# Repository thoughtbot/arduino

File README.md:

arduino
=======

Public repo for thoughtbot custom Arduino board

Refer to these blog posts for instructions:

[Low Power Custom Arduino Sensor Board](http://robots.thoughtbot.com/low-power-custom-arduino-sensor-board)

[Arduino Sensor Network](http://robots.thoughtbot.com/arduino-sensor-network)

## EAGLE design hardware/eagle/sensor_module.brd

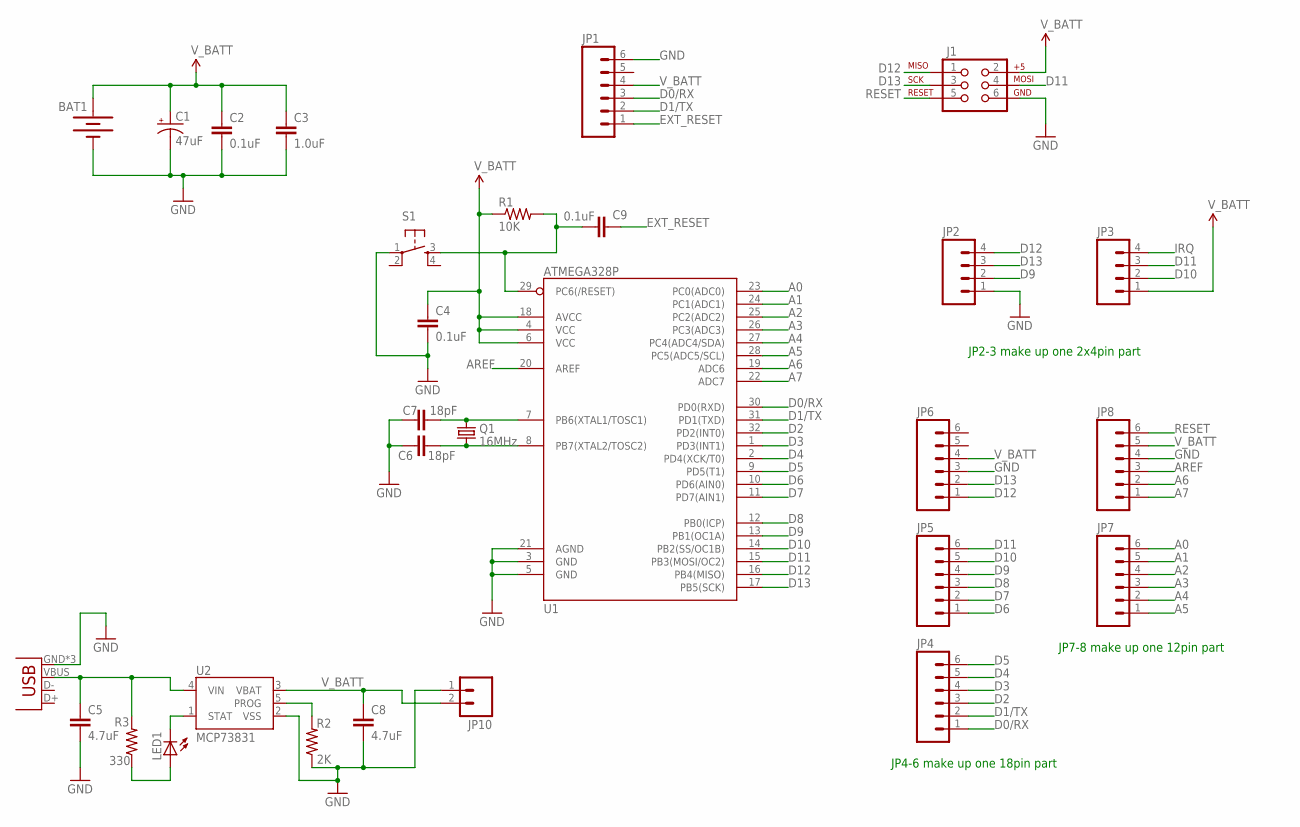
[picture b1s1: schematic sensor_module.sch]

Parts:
BAT1: 20mm coincell; BATTCON_20MM_4LEGS
C1: 47uF; EIA3216
C2, C4, C9: 0.1uF; 0603-CAP
C3: 1.0uF; 0603-CAP
C5, C8: 4.7uF; 0603-CAP
C6, C7: 18pF; 0603-CAP
J1: AVR_SPI_PRG_6PTH; 2X3
JP1, JP4, JP5, JP6, JP7, JP8: M06SIP; 1X06
JP2, JP3: M04PTH; 1X04
JP9: USB-MICROB
JP10: M02JST-PTH-2; JST-2-PTH
LED1: LED_ESML0603; LED_SML0603
Q1: 16MHz; HC49UP
R1: 10K; 0603-RES
R2: 2K; 0603-RES
R3: 330; 0603-RES
S1: TAC_SWITCHSMD; TACTILE_SWITCH_SMD
U1: ATMEGA328P; TQFP32-08
U2: MCP73831; SOT23-5

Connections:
A0: JP7.6, U1.23 (PC0(ADC0))
A1: JP7.5, U1.24 (PC1(ADC1))
A2: JP7.4, U1.25 (PC2(ADC2))
A3: JP7.3, U1.26 (PC3(ADC3))
A4: JP7.2, U1.27 (PC4(ADC4/SDA))
A5: JP7.1, U1.28 (PC5(ADC5/SCL))
A6: JP8.2, U1.19 (ADC6)
A7: JP8.1, U1.22 (ADC7)
AREF: JP8.3, U1.20 (AREF)
D0/RX: JP1.3, JP4.1, U1.30 (PD0(RXD))
D1/TX: JP1.2, JP4.2, U1.31 (PD1(TXD))
D2: JP4.3, U1.32 (PD2(INT0))
D3: JP4.4, U1.1 (PD3(INT1))
D4: JP4.5, U1.2 (PD4(XCK/T0))
D5: JP4.6, U1.9 (PD5(T1))
D6: JP5.1, U1.10 (PD6(AIN0))
D7: JP5.2, U1.11 (PD7(AIN1))
D8: JP5.3, U1.12 (PB0(ICP))
D9: JP2.2, JP5.4, U1.13 (PB1(OC1A))
D10: JP3.2, JP5.5, U1.14 (PB2(SS/OC1B))
D11: J1.4, JP3.3, JP5.6, U1.15 (PB3(MOSI/OC2))
D12: J1.1, JP2.4, JP6.1, U1.16 (PB4(MISO))
D13: J1.3, JP2.3, JP6.2, U1.17 (PB5(SCK))
EXT_RESET: C9.1, JP1.1
GND: BAT1.2 (-), C1.C (-), C2.2, C3.2, C4.2, C5.2, C6.1, C7.2, C8.2, J1.6, JP1.6, JP2.1, JP6.3, JP8.4, JP9.GND, JP9.MT1 (GND), JP9.MT2 (GND), JP10.1, R2.1, S1.1, U1.3 (GND), U1.5 (GND), U1.21 (AGND), U2.2 (VSS)
IRQ: JP3.4
unnamed: C7.1, Q1.1, U1.7 (PB6(XTAL1/TOSC1))
unnamed: C6.2, Q1.2, U1.8 (PB7(XTAL2/TOSC2))
unnamed: LED1.C, U2.1 (STAT)
unnamed: LED1.A, R3.1
unnamed: C5.1, JP9.VBUS, R3.2, U2.4 (VIN)
unnamed: R2.2, U2.5 (PROG)
RESET: C9.2, J1.5, JP8.6, R1.2, S1.3, U1.29 (PC6(/RESET))
V_BATT: BAT1.1 (+), C1.A (+), C2.1, C3.1, C4.1, C8.1, J1.2, JP1.4, JP3.1, JP6.4, JP8.5, JP10.2, R1.1, U1.4 (VCC), U1.6 (VCC), U1.18 (AVCC), U2.3 (VBAT)

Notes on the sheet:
JP4-6 make up one 18pin part
JP7-8 make up one 12pin part
JP2-3 make up one 2x4pin part

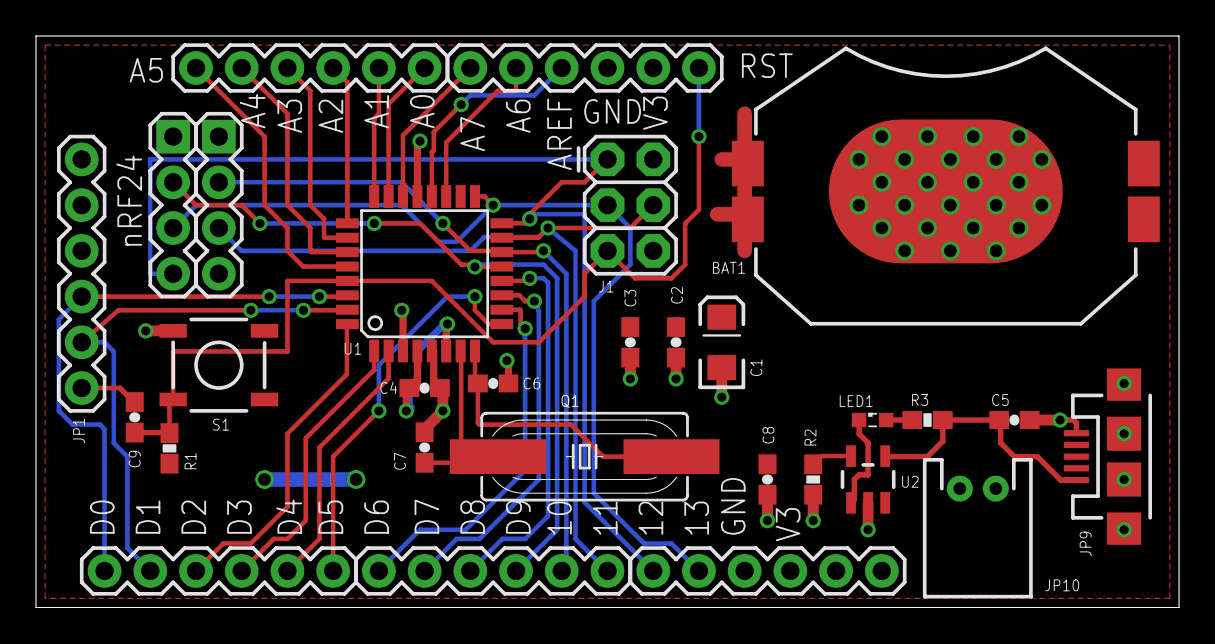
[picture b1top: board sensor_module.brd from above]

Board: 2 copper layers, 63.5 x 31.8 mm, 29 parts (0 on the bottom side), 33 nets.

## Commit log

2014-02-17 Add hardware schematic, PCB, gerbers, and BOM
2014-02-17 Add software library
2014-02-17 Update schematic to latest values and include PDF
2014-02-17 Fix capacitor type on BOM
2014-02-18 Add client and hub examples
2014-02-27 Cleanup watchdog timer interrup and registers
2014-03-05 Add blog posts to readme

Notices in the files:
parts and their libraries:
SparkFun-DigitalIC: Licensing: CC v3.0 Share-Alike You are welcome to use this library for commercial purposes.
